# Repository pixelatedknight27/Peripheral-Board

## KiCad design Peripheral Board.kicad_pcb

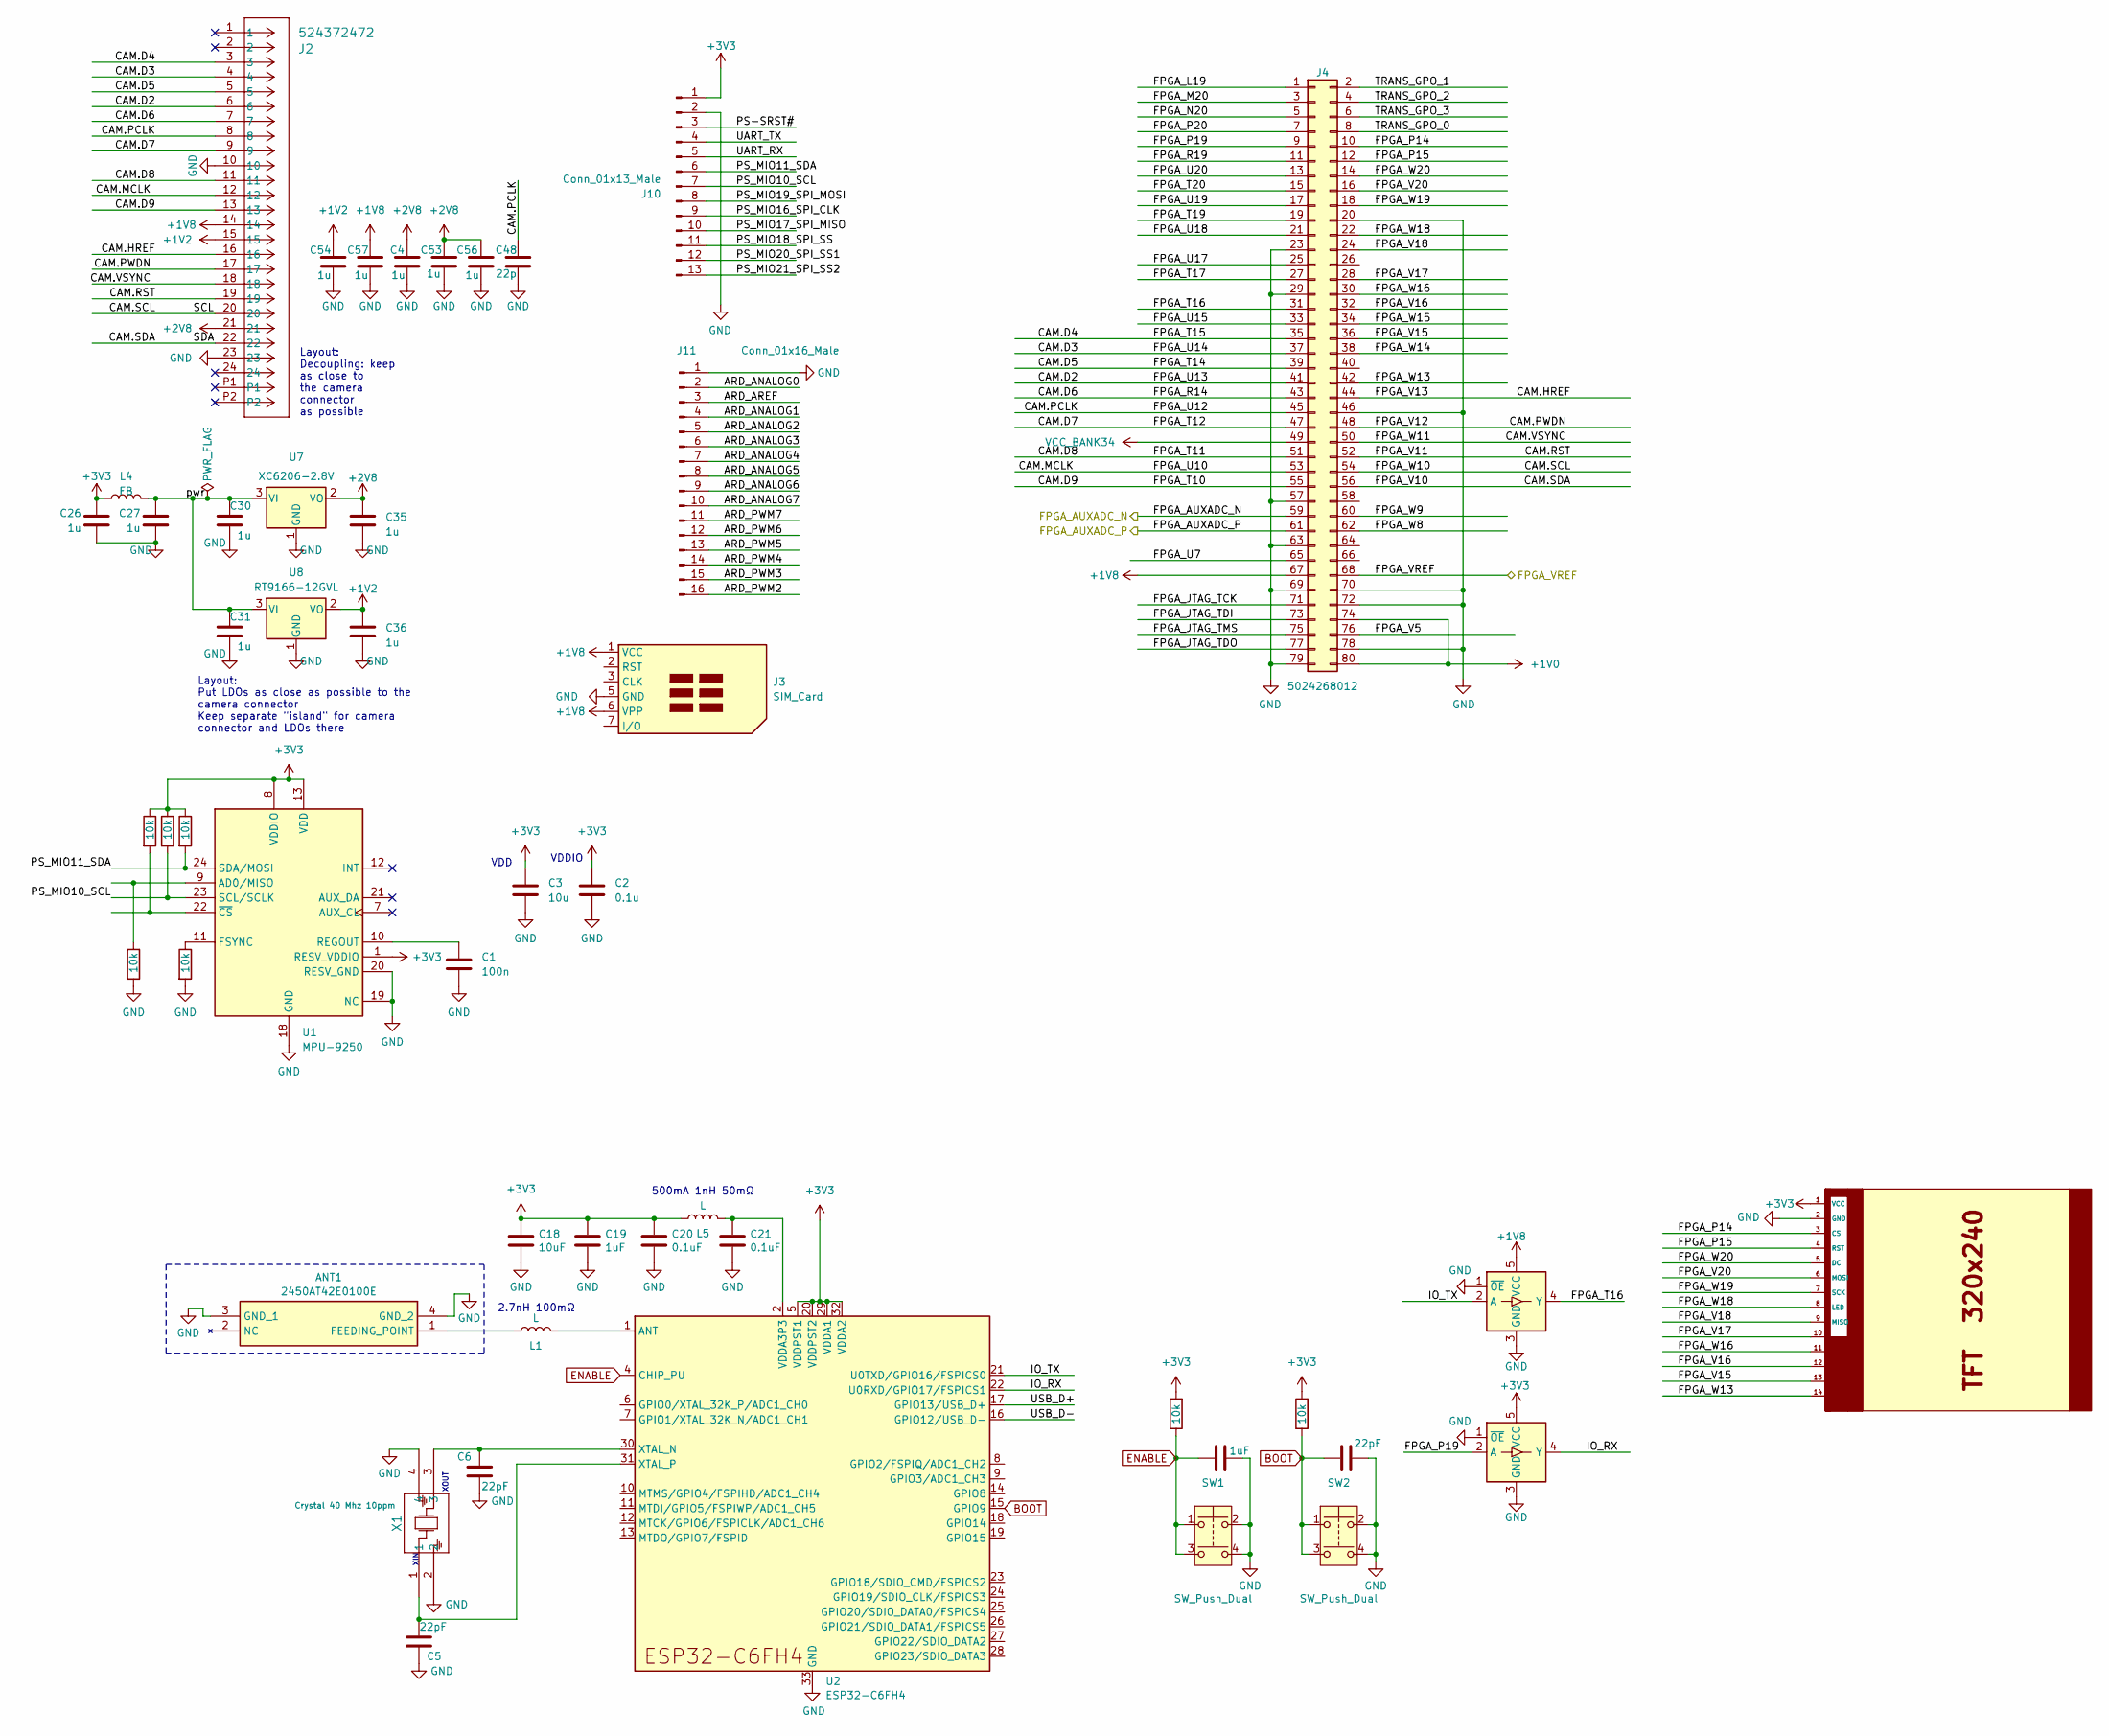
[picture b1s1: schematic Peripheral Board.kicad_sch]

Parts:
ANT1: 2450AT42E0100E; 2450AT42E0100E-ANT; LCSC C3285081
C1: 100n; C_0402_1005Metric_Pad0.74x0.62mm_HandSolder; LCSC C77020
C2, C3, C26, C27, C30, C31, C35, C36, C53: 10u_0402_CL05A105KA5NQNC; C_0402_1005Metric; Rating 25V; Tolerance 10%; MPN CL05A105KA5NQNC
C4, C54, C56, C57: 10u_0402_CL05A105KA5NQNC; C_0402_1005Metric; Tolerance 10%; Rating 25V; MPN CL05A105KA5NQNC
C5, C6, C23: 22pF; C_0402_1005Metric; LCSC C5119318
C7, C19: 1uF; C_0402_1005Metric; LCSC C162161
C18: 10uF; C_0402_1005Metric; LCSC C15850
C20, C21: 0.1uF; C_0402_1005Metric; LCSC C327087
C48: 22p_0402_0402CG220J500NT; C_0402_1005Metric; Rating 50V; Tolerance 5%; MPN 0402CG220J500NT
J2: 524372472; CON_524372472_MOL
J3: SIM_Card; nanoSIM_GCT_SIM8060-6-0-14-00
J4: 5024268012; Molex_SlimStack_502430-8010_2x40_P0.40mm_Vertical
J10: Conn_01x13_Male; PinHeader_1x13_P2.54mm_Vertical
J11: Conn_01x16_Male; PinHeader_1x16_P2.54mm_Vertical
L1: L; L_0603_1608Metric; LCSC C5252358
L4: FB_2A_0805_220R@100MHz_BLM21PG221SN1D; L_0805_2012Metric_Pad1.15x1.40mm_HandSolder; Rating 2A; MPN BLM21PG221SN1D
L5: L; L_0603_1608Metric; LCSC C1027
R2, R18: 10k; R_0402_1005Metric; LCSC C4322213
R10, R11, R15, R16, R17: 10k; R_0402_1005Metric; LCSC C25543
SW1, SW2: SW_Push_Dual; switch_SKSVCCE010; LCSC C325005
U1: MPU-9250; InvenSense_QFN-24_3x3mm_P0.4mm
U2: ESP32-C6FH4; QFN-32-1EP_5x5mm_P0.5mm_EP3.6x3.6mm; LCSC C6908287
U3, U4: SN74LV1T125DBV; SOT-23-5
U5: TFT_320x240; TFT-320x240
U7: XC6206-2.8V; SOT-23; MPN XC6206-2.8V
U8: RT9166-12GVL; SOT-23; MPN RT9166-12GVL
X1: Crystal 40 Mhz 10ppm; Crystal_ECS-40Mhz_ECS; LCSC C555614

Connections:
+1V0: J4.74, J4.80
+1V2: C36.1, C54.2, J2.15, U8.2 (VO)
+1V8: C57.2, J2.14, J3.1 (VCC), J3.6 (VPP), J4.67, U3.5 (VCC)
+2V8: C4.2, C35.1, C53.1, C56.2, J2.21, U7.2 (VO)
+3V3: C2.1, C3.1, C18.2, C19.2, C20.2, C26.1, J10.1, L4.1, L5.1, R2.2, R10.1, R11.1, R15.1, R18.2, U1.1 (RESV_VDDIO), U1.8 (VDDIO), U1.13 (VDD), U2.5 (VDDPST1), U2.20 (VDDPST2), U2.29 (VDDA1), U2.32 (VDDA2), U4.5 (VCC), U5.1 (VCC)
/ARD_ANALOG0: J11.2
/ARD_ANALOG1: J11.4
/ARD_ANALOG2: J11.5
/ARD_ANALOG3: J11.6
/ARD_ANALOG4: J11.7
/ARD_ANALOG5: J11.8
/ARD_ANALOG6: J11.9
/ARD_ANALOG7: J11.10
/ARD_AREF: J11.3
/ARD_PWM2: J11.16
/ARD_PWM3: J11.15
/ARD_PWM4: J11.14
/ARD_PWM5: J11.13
/ARD_PWM6: J11.12
/ARD_PWM7: J11.11
/CAM.D2: J2.6, J4.41
/CAM.D3: J2.4, J4.37
/CAM.D4: J2.3, J4.35
/CAM.D5: J2.5, J4.39
/CAM.D6: J2.7, J4.43
/CAM.D7: J2.9, J4.47
/CAM.D8: J2.11, J4.51
/CAM.D9: J2.13, J4.55
/CAM.HREF: J2.16, J4.44
/CAM.MCLK: J2.12, J4.53
/CAM.PCLK: C48.1, J2.8, J4.45
/CAM.PWDN: J2.17, J4.48
/CAM.RST: J2.19, J4.52
/CAM.SCL: J2.20, J4.54
/CAM.SDA: J2.22, J4.56
/CAM.VSYNC: J2.18, J4.50
/FPGA_AUXADC_N: J4.59
/FPGA_AUXADC_P: J4.61
/FPGA_JTAG_TCK: J4.71
/FPGA_JTAG_TDI: J4.73
/FPGA_JTAG_TDO: J4.77
/FPGA_JTAG_TMS: J4.75
/FPGA_L19: J4.1
/FPGA_M20: J4.3
/FPGA_N20: J4.5
/FPGA_P14: J4.10, U5.3 (CS)
/FPGA_P15: J4.12, U5.4 (RST)
/FPGA_P19: J4.9, U4.2 (A)
/FPGA_P20: J4.7
/FPGA_R19: J4.11
/FPGA_T16: J4.31, U3.4 (Y)
/FPGA_T17: J4.27
/FPGA_T19: J4.19
/FPGA_T20: J4.15
/FPGA_U7: J4.65
/FPGA_U15: J4.33
/FPGA_U17: J4.25
/FPGA_U18: J4.21
/FPGA_U19: J4.17
/FPGA_U20: J4.13
/FPGA_V5: J4.76
/FPGA_V15: J4.36, U5.13
/FPGA_V16: J4.32, U5.12
/FPGA_V17: J4.28, U5.10
/FPGA_V18: J4.24, U5.9 (MISO)
/FPGA_V20: J4.16, U5.6 (MOSI)
/FPGA_VREF: J4.68
/FPGA_W8: J4.62
/FPGA_W9: J4.60
/FPGA_W13: J4.42, U5.14
/FPGA_W14: J4.38
/FPGA_W15: J4.34
/FPGA_W16: J4.30, U5.11
/FPGA_W18: J4.22, U5.8 (LED)
/FPGA_W19: J4.18, U5.7 (SCK)
/FPGA_W20: J4.14, U5.5 (DC)
/IO_RX: U2.22 (U0RXD/GPIO17/FSPICS1), U4.4 (Y)
/IO_TX: U2.21 (U0TXD/GPIO16/FSPICS0), U3.2 (A)
/PS-SRST#: J10.3
/PS_MIO10_SCL: J10.7, R11.2, U1.23 (SCL/SCLK)
/PS_MIO11_SDA: J10.6, R10.2, U1.24 (SDA/MOSI)
/PS_MIO16_SPI_CLK: J10.9
/PS_MIO17_SPI_MISO: J10.10
/PS_MIO18_SPI_SS: J10.11
/PS_MIO19_SPI_MOSI: J10.8
/PS_MIO20_SPI_SS1: J10.12
/PS_MIO21_SPI_SS2: J10.13
/TRANS_GPO_0: J4.8
/TRANS_GPO_1: J4.2
/TRANS_GPO_2: J4.4
/TRANS_GPO_3: J4.6
/UART_RX: J10.5
/UART_TX: J10.4
/USB_D+: U2.17 (GPIO13/USB_D+)
/USB_D-: U2.16 (GPIO12/USB_D-)
/pwr: C27.1, C30.1, C31.1, L4.2, U7.3 (VI), U8.3 (VI)
BOOT: C23.1, R18.1, SW2.1, SW2.3, U2.15 (GPIO9)
ENABLE: C7.2, R2.1, SW1.1, SW1.3, U2.4 (CHIP_PU)
GND: ANT1.3 (GND_1), ANT1.4 (GND_2), C1.2, C2.2, C3.2, C4.1, C5.1, C6.2, C7.1, C18.1, C19.1, C20.1, C21.1, C23.2, C26.2, C27.2, C30.2, C31.2, C35.2, C36.2, C48.2, C53.2, C54.1, C56.1, C57.1, J2.10, J2.23, J3.5 (GND), J4.20, J4.23, J4.29, J4.46, J4.57, J4.63, J4.69, J4.70, J4.72, J4.78, J4.79, J10.2, J11.1, R16.2, R17.2, SW1.2, SW1.4, SW2.2, SW2.4, U1.18 (GND), U1.19 (NC), U1.20 (RESV_GND), U2.33 (GND), U3.1 (~OE), U3.3 (GND), U4.1 (~OE), U4.3 (GND), U5.2 (GND), U7.1 (GND), U8.1 (GND), X1.2, X1.4
unnamed: ANT1.1 (FEEDING_POINT), L1.1
unnamed: C21.2, L5.2, U2.2 (VDDA3P3), U2.3 (VDDA3P3)
unnamed: R17.1, U1.9 (AD0/MISO)
unnamed: R16.1, U1.11 (FSYNC)
unnamed: C1.1, U1.10 (REGOUT)
unnamed: R15.2, U1.22 (~CS)
unnamed: L1.2, U2.1 (ANT)
unnamed: C6.1, U2.30 (XTAL_N), X1.3
unnamed: C5.2, U2.31 (XTAL_P), X1.1
VCC_BANK34: J4.49

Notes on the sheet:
XIN
2.7nH 100mΩ
VDD
Layout: Decoupling: keep as close to the camera connector as possible
XOUT
Layout: Put LDOs as close as possible to the camera connector Keep separate "island" for camera connector and LDOs there
500mA 1nH 50mΩ
VDDIO

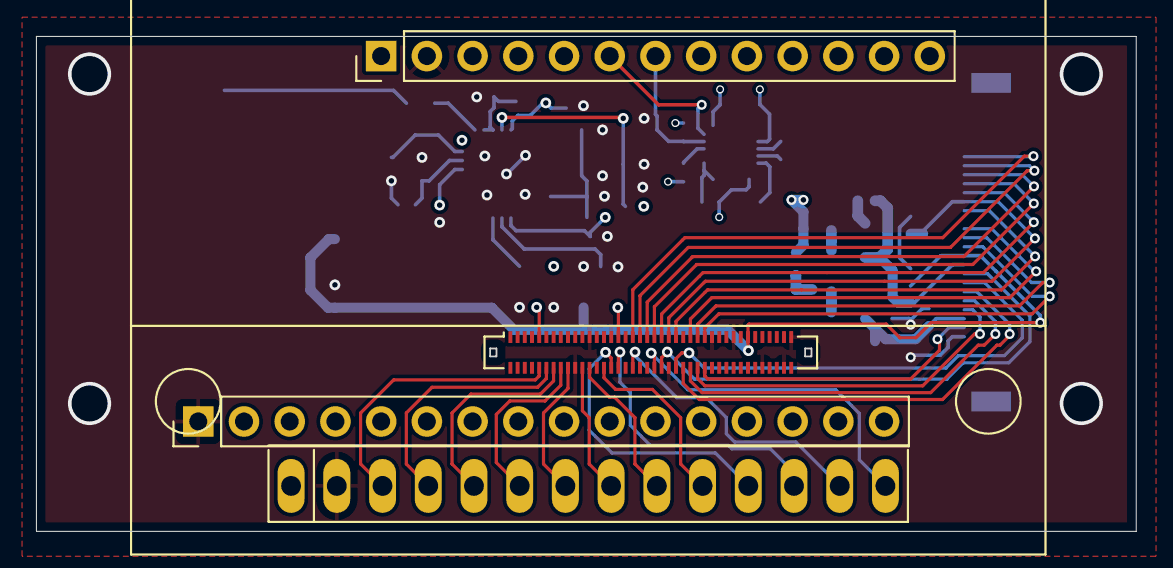
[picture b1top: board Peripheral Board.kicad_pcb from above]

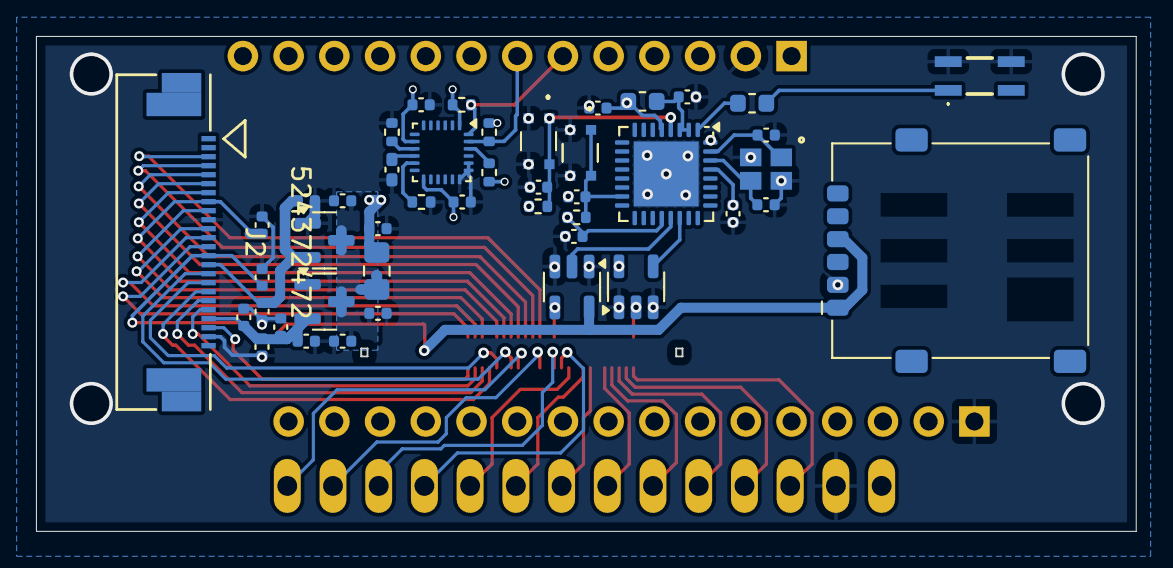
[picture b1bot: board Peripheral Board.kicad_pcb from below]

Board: 4 copper layers, 61.1 x 27.5 mm, 49 parts (45 on the bottom side), 52 nets.

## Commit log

2026-03-06 add routing
2026-03-11 Added sd card, routed camera, and added esp32c3
